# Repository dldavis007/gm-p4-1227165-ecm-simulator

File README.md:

# BUA / GM 1227165 Step-171 evidence-supported whole-image closure

## Current status

The supplied 9340 / 16059335 PROM image has an evidence-supported behavioral
C89 translation with no known reachable, internally defined executable area
remaining classified as unported. This is not a claim of cycle-exact processor
emulation or electrical equivalence to the original ECM.

- [Current project status](docs/CURRENT_PROJECT_STATUS.md)
- [Formal theory of operation](THEORY_OF_OPERATION.md)
  ([PDF publication](THEORY_OF_OPERATION.pdf))
- [Documentation hub](docs/README.md)
- [Simulator, build, and testing guide](docs/SIMULATOR_BUILD_TEST_GUIDE.md)
- [Embedded and HIL implementation roadmap](docs/EMBEDDED_HIL_IMPLEMENTATION_ROADMAP.md)
- [Step history index](docs/STEP_HISTORY_INDEX.md)
- [Technical-reference index](docs/reference/README.md)
- [Step 171 closure audit](docs/STEP171_WHOLE_IMAGE_RECLOSURE_AUDIT.txt)

New behavioral work requires a newly identified exact listing discrepancy or
new primary evidence. Embedded/HIL implementation is a separate phase at the
documented HAL boundaries.

## Development history

This retains the modular frozen Step-104 C89 PC harness, independent Step-105
transmission-aware driving scenario, and Step-106 listing correction.  Step
107 begins the listing-backed translation of Major Segment D diagnostics,
Step 108 translates its complete `LE4F7..LE75C` qualification chain, and Step
109 completes the field-service and flash-code routes and scheduler wiring.
Step 110 audits the remaining executable image and completes the listing-exact
Segment-1 MPU/I/O output staging at `$EDA3..$EF03`. Step 111 translates and
scheduler-wires the key-off front at `$D6D1..$D769`, the LF447 block-learn
commit, the IAC reset/park state machine at `$D370..$D3DB`, and a thin HAL
event at the software-powerdown endpoint.
Step 112 adds a listing-only, source-ordered model of `$C800..$C9F3`, including
the normal scheduler handoff and explicit boundaries for factory test, the
optional HUD ROM, SWI wait, MPU peripherals, and 8192-baud service. It does
not use `bua-hac.txt` as firmware evidence.
Step 113 translates the exact LF3A7 retained-error checksum and LF434 BLM/SAM
initialization, corrects the live LF434 default from historical decimal 120 to
the emitted `$80` (128), and preserves the older value only inside explicit
Step-104/105/109 signature replays.
Step 114 integrates the listing-ordered normal startup initializer at
`$C93B..$C9F3` through a distinct power-on entry point. It reuses established
coolant, TPS and Segment-E behavior, preserves the direct SCI/MPU/timer writes,
and leaves the unresolved SCI device-control-block walk as a named boundary.
Step 115 resolves that device-control-block initialization and translates the
listing's sole device `$80` receive, validation, checksum, Modes 0–4, response,
and transmit-state core. Physical byte timing and unrepresented ROM reads stay
behind explicit PC/HAL boundaries.
Step 116 connects completed SCI messages to the source-ordered `$CB5F..$CBB4`
Mode-4 scheduler lifecycle and `$CBCA..$CBD9` communication timeout. Mode-4
activation now occurs after reception, and entry-only error, IAC and BLM reset
commands execute exactly once.
Step 117 integrates the factory-test boot and IRQ control path at
`$C8B2..$C8DF`, `$CA6F..$CA73`, and `$FC72..$FD28`. It preserves the emitted
factory data-pointer table, optional `$AA` RAM fill, FMD exchange boundary,
96-count minor loop, serial cadence selection, battery/ignition decisions, and
literal COP restart. Custom-control and physical output exercises beginning at
`$FD29` remain a separate hardware-facing step.
Step 118 completes the listing-backed factory-test execution loop at
`$FD29..$FEA3`. It preserves the raw numeric mode-bit branches, nonvolatile
RAM checksum, twelve-channel A/D capture, alternating coolant pull-up samples,
six-channel PWM exercise, lamp/fan and IAC bit sequences, and the three exact
reference-period fuel/spark branches. Electrical effects and the final wait
loop remain HAL boundaries.
Step 119 preserves the eight emitted vector words at `$FFF0..$FFFE`, connects
the `$C9F4` slot to ordinary/factory IRQ dispatch, confirms `$F27B` is an
immediate `RTI`, and represents the four `$C800` destinations as reset/startup
requests. Both `$6000` targets and the processor-specific SWI-to-slot mapping
remain explicit boundaries rather than comment-derived assumptions.
Step 120 composes the previously audited startup pieces into one live,
source-ordered `$C800..$C9F3` power-on dispatcher. It preserves retained RAM
until validation, clears the exact volatile ranges, selects factory test
before retained recovery, records the absent HUD ROM and `$C938` SWI as
boundaries, and hands normal boots to the Step-114 initializer. ROM checksum,
socket-check result, and hardware samples remain explicit host/HAL inputs.
Step 121 connects reset-vector power-on, normal IRQ operation, ignition-off
shutdown, BLM commit, IAC homing, the software-powerdown boundary, and a later
retained restart in one end-to-end PC/HAL lifecycle. It also proves corrupted
retained recovery and factory-path isolation. Physical power switching and
processor reset consequences remain explicitly acknowledged HAL boundaries.
Step 122 re-audited the complete assembled image after the Step-111 through
Step-121 integrations and initially found no known reachable, internally
defined firmware area still classified as unported. Step 167 later narrowed
that conclusion after identifying the missing LF880 factory and diagnostic
table branches. Steps 168 and 169 translate those exact listing-backed gaps,
Step 170 exposes the completed manager through a cell-level raw HAL, and Step
171 restores the qualified whole-image closure conclusion. Remaining limits
are calibration/data, external or absent ROM, processor/custom-device behavior,
and physical electrical/timing boundaries rather than known unported behavior.
Step 123 inventories the historical Library/Drive evidence before cleanup. It
confirms the committed assembled listing, identifies the six ECM schematic
sheets and MEMCAL records awaiting controlled import, classifies duplicate
candidates and historical Step packages, and records the missing original
PROM/S-record comparison artifact. It changes no behavioral code and authorizes
no Library deletion.
Step 124 imports one hash-verified copy of each of the six ECM schematic sheets,
the MEMCAL photograph, connection notes, and resistor notes. It proves the
numbered schematic and photograph copies byte-identical, preserves all variant
and provenance limitations, and still authorizes no historical-file deletion.
Step 125 audits seven unique historical Step-104/105/109/110/111 packages,
proves the two Step-111 ZIPs byte-identical, and records how their source,
output, warning, audit, and signature content relates to the active repository.
The redundant packages are intentionally not committed. It changes no
behavioral code and performs no historical-file deletion.
Step 126 closes the MEMCAL/source-provenance investigation supportable from the
retained evidence. It clarifies the 66-contact MEMCAL carrier, documents the
14-terminal 16055375 and 16-terminal 16055376 network reconstructions and their
zero-ohm routing-jumper scheme, adds historical package-geometry corroboration,
and verifies the corrected `bua-hac.asm -> bua-hac.lst / bua-hac.s19 /
bua-hac.bin` build relationship. The authoritative listing remains the primary
repository byte/address evidence. Physical carrier continuity and installed-
resistor checks remain explicitly deferred hardware measurements rather than
Step-126 blockers.
Step 127 classifies the remaining hardware-facing simulator interfaces by
fidelity: listing-exact firmware/raw-register behavior, schematic-connected
hardware, processor-visible HAL signals, simulator-only plant/transfer
assumptions, and external/unknown device boundaries. It confirms that no new
translated-core behavior is required by the current evidence and prioritizes
explicit HAL setters/observers as the safest next implementation work.
Step 128 adds that explicit HAL seam around already-established raw inputs and
outputs. It introduces named setters/observers for O2, battery, VSS, reference
RPM, bounded RAM, MPU, parallel-I/O and related raw state without adding new
electrical semantics, vehicle-plant behavior, or custom-device assumptions.
Step 129 converts the reverse-engineered MEMCAL resistor networks from generic
grid layouts into functional terminal-level networks, closes the physical
66-pin carrier-to-J4 mapping, and establishes photograph-first authority for
as-built resistor and zero-ohm-jumper population. It also closes the 16055376
24-kOhm discrepancy in favor of the photographed hardware and LTspice model.
Step 130 carries those MEMCAL mappings through the motherboard and into
listing-backed firmware behavior. It establishes evidence-linked CAL42/OSC,
CAL56/CYL, CAL61/MAP, CAL59/VIGN and ESC/KNOCK paths while keeping U11/U12
internal transfer functions and resistor-only semantics explicitly unresolved.
Step 131 traces the visible ignition and injection chain around U9, U11 and
U12. It attributes the `$3FC0-$3FFF` window to U9 at the device level, closes
the supported processor-visible reference/RPM, spark/EST and injector-command
paths, and leaves exact pin-to-register mapping, polarity, phase and current
control as custom-device boundaries.
Step 132 separates the physical MAP/MAP2 and CAL61/U11 paths from the supplied
image's actual MAF/reference-period load producer. It establishes `$0063` as a
MAF-derived load quantity for this image and preserves U11 MAP/CAL61 behavior
and variant-dependent MAP use as unresolved.
Step 133 maps the visible U10 A/D channels to schematic signals, normal
firmware selectors, factory-test capture, raw RAM state and processed behavior.
It distinguishes MAP2, VOLT, O2, MAP, CTS, TPS, PUMPVOLT, DIAG, MAT, ESC and
VMAF channels and records which selectors the normal image actually requests.
Step 134 separates CAL42/U11 OSC, CAL56/U12 CYL and the distributor-reference
path. It cross-references reference occurrence, period and RPM processing while
preserving U11/U12/U9 internal behavior and CAL56 voltage encoding as explicit
unknowns.
Step 135 separates the CAL29/U10 analog ESC monitor from the CAL32/U12/U9
knock-event path and traces the executable knock-retard, recovery, spark
subtraction and Error-43 behavior. The U9 KNOCK-pin-to-`$3FCA` relationship is
kept as a strong inference rather than promoted to undocumented direct proof.

The project targets the 1986 Corvette L98 GM P4 ECM, service number 1227165, using the
supplied 9340 / 16059335 PROM material.  `BUA` remains a source label, not an
independently proven calibration identity.

## Build

The project deliberately builds as one translation unit:

```text
gcc -std=c89 -Wall -Wextra -pedantic main.c -o build/bua_step121
```

The included implementation fragments must not be compiled separately.
`main.c` includes them in the frozen declaration order so all existing
file-local (`static`) linkage and arithmetic behavior remain unchanged.

- Windows compile: run `build_gcc.bat`
- Windows compile and run: run `build_run_gcc.bat`
- Linux/macOS compile and run: run `sh build_gcc.sh`
- Make: run `make test`

For OnlineGDB, import the complete project tree and compile only `main.c`.
Every source fragment is well below the previously observed approximately
11,000-line editor/save limit.  `main.c` itself contains `int main(void)`.

## Directory layout

| Path | Purpose |
| --- | --- |
| `main.c` | Readable include map and program entry point |
| `src/` | Translated ECM algorithms, scheduler, RAM/MPU model, and feature wiring |
| `simulation/` | Original scripted drive plus the PC-only transmission-aware plant |
| `tests/` | Regression models and regression functions |
| `docs/` | Frozen evidence and numbered step audits |
| `docs/reference/` | Living evidence register, hardware/firmware cross-reference, MEMCAL model, and theory-of-operation index |
| `evidence/firmware/` | Authoritative assembled listing and corrected-source/build provenance record |
| `evidence/hardware/` | Hash-identified ECM schematic evidence with provenance and interpretation limits |
| `evidence/memcal/` | Hash-identified MEMCAL photograph, connection notes, resistor evidence, and reconstruction records |
| `build/` | Generated executables, output, and compiler diagnostics |

Files ending in `.inc.h` are implementation fragments, not independent public
headers.  The naming makes that constraint explicit while preventing online
compilers from treating them as separate C source files.

## Behavioral baselines

- Frozen Step-104 behavioral signature: `4BA6B7C6`
- Step-105 transmission trace signature: `9732D09B`
- Step-106 listing-coolant regression: 12/12
- Step-107 diagnostic-stage regression: 17/17
- Step-108 diagnostic-qualification regression: 22/22
- Step-109 integrated Segment-D regression: 40/40
- Step-109 integrated Segment-D signature: `F357A5F2`
- Step-110 Segment-1 output regression: 22/22
- Step-110 integrated output-stage signature: `FAADF8A6`
- Step-111 ignition shutdown/IAC homing regression: 40/40
- Step-111 ignition lifecycle signature: `16D17C9C`
- Step-112 source-ordered reset/startup regression: 19/19
- Step-113 retained-memory/startup regression: 10/10
- Step-114 source-ordered normal-startup regression: 14/14
- Step-115 8192-baud SCI/message regression: 20/20
- Step-116 Mode-4 lifecycle/scheduler regression: 16/16
- Step-117 factory-test boot/control regression: 24/24
- Step-118 factory-test execution regression: 31/31
- Step-119 vector/exception-boundary regression: 19/19
- Step-120 unified power-on-dispatch regression: 24/24
- Step-121 end-to-end ignition-lifecycle integration: 18/18
- Step-158 normal-operation FMD raw HAL regression: 7/7
- Step-159 raw-HAL lifecycle integration regression: 8/8
- Step-160 full raw-HAL lifecycle integration regression: 13/13
- Step-160 full raw-HAL lifecycle signature: `2E92563C`
- Step-161 raw-HAL output lifecycle regression: 9/9
- Step-161 raw-HAL output lifecycle signature: `B22B98ED`
- Step-162 raw-VOLT output-safety regression: 10/10
- Step-162 raw-VOLT output-safety signature: `DB86F332`
- Step-163 raw-HAL power-on composition regression: 10/10
- Step-163 raw-HAL power-on signature: `040E3A8B`
- Step-164 raw-HAL factory IRQ regression: 10/10
- Step-164 raw-HAL factory IRQ signature: `0194B153`
- Step-165 raw-HAL factory A/D regression: 9/9
- Step-165 raw-HAL factory A/D signature: `0EACFF4F`
- Step-166 8192-baud SCI raw-HAL regression: 9/9
- Step-166 8192-baud SCI raw-HAL signature: `52396771`
- Step-168 diagnostic 160-baud manager regression: 6/6
- Step-169 factory 160-baud manager regression: 8/8
- Step-170 complete 160-baud raw-HAL regression: 9/9
- Strict C89 compile: no warnings
- Integrated drive regression: 26/26
- Step-104 freeze regression: 10/10
- Step-105 transmission-aware regression: 12/12

The original Step-104 scenario remains present and unchanged.  Step 105 runs
after a fresh reset and derives Drive RPM from vehicle speed, selected ratio,
converter slip, and physical TCC state.  Its shift points, slip, and combined
axle/tire factor are explicitly simulator parameters, not factory claims.

The listing proves that LF42A is an RTS at $F42A.  It also proves that the
assembled ERR14/15 fallback at $F418 branches to LF42A; the `COOLS8` spelling
in the supplied text is not an unresolved executable destination.

See `docs/STEP121_LIFECYCLE_INTEGRATION_AUDIT.txt` for the end-to-end lifecycle
integration audit and `docs/STEP122_WHOLE_IMAGE_CLOSURE_AUDIT.txt` for the
post-integration coverage conclusion. See
`docs/STEP123_LIBRARY_EVIDENCE_INVENTORY.txt` for the pre-cleanup archive gate.
See `docs/STEP124_CONTROLLED_EVIDENCE_IMPORT.txt` for the imported artifact
manifest and duplicate proof. See
`docs/STEP125_HISTORICAL_PACKAGE_AUDIT.txt` for the package-level
manifest and preservation decisions. See
`docs/STEP126_MEMCAL_AND_SOURCE_PROVENANCE_CLOSURE_AUDIT.txt` for the MEMCAL,
corrected-source, build-output, and historical-PROM provenance closure. See
`docs/STEP127_HARDWARE_HAL_FIDELITY_AUDIT.txt` for the hardware/HAL fidelity
classification. See `docs/STEP128_EXPLICIT_HAL_INTERFACE_AUDIT.txt` for the
explicit raw HAL boundary and `docs/STEP129_MEMCAL_FUNCTIONAL_NETWORK_AUDIT.txt`
for the functional MEMCAL reconstruction and physical carrier mapping. See
`docs/STEP130_MEMCAL_MOTHERBOARD_FIRMWARE_CROSS_REFERENCE_AUDIT.txt` through
`docs/STEP135_ESC_KNOCK_SIGNAL_CHAIN_AUDIT.txt` for the current motherboard,
custom-device, sensor-acquisition, timing and ESC/knock theory-of-operation
cross-reference work. See `docs/STEP158_NORMAL_FMD_RAW_HAL_AUDIT.txt` for the
normal-operation FMD/SPI raw-input boundary and
`docs/STEP159_RAW_HAL_LIFECYCLE_INTEGRATION_AUDIT.txt` for its integration with
the raw VOLT ignition path. See
`docs/STEP160_FULL_RAW_HAL_LIFECYCLE_AUDIT.txt` for the full key-off, IAC homing,
powerdown, and retained-restart acceptance cycle, and
`docs/STEP161_RAW_HAL_OUTPUT_LIFECYCLE_AUDIT.txt` for the corresponding raw
output-window shutdown and restart contract, and
`docs/STEP162_RAW_VOLT_OUTPUT_SAFETY_AUDIT.txt` for the scheduler-driven
two-pass overvoltage output shutdown, and
`docs/STEP163_RAW_HAL_POWER_ON_COMPOSITION_AUDIT.txt` for raw VOLT, PUMPVOLT,
DIAG, and FMD startup selection, and
`docs/STEP164_RAW_HAL_FACTORY_IRQ_AUDIT.txt` for continued raw-input ownership
during factory IRQ execution, and
`docs/STEP165_RAW_HAL_FACTORY_ADC_AUDIT.txt` for the live eleven-channel named
factory sweep with the unidentified `$B0` slot preserved, and
`docs/STEP166_SCI8192_RAW_HAL_AUDIT.txt` for the message-level receive/response
boundary around the translated 8192-baud SCI core, and
`docs/STEP167_ALDL160_COMPLETENESS_AUDIT.txt` for the corrected scope of the
normal, diagnostic and factory 160-baud byte-manager paths.
Steps 168 and 169 close both table-manager gaps;
`docs/STEP170_ALDL160_RAW_HAL_AUDIT.txt` records the resulting cell-level raw
HAL boundary, and `docs/STEP171_WHOLE_IMAGE_RECLOSURE_AUDIT.txt` reconciles the
whole-image closure conclusion. Earlier audits remain historical checkpoints.

Normal simulator execution now runs Segment D once per 16 ordinary IRQs. The
PC-only `sim_legacy_segment_d_freeze` switch is enabled only inside the frozen
Step-104 and Step-105 replay scenarios, so their historical signatures remain
comparable. It is not source RAM and is not part of the target ECM behavior.

Normal simulator execution now also performs Segment 1's raw writes to MPU
addresses `$3FCC/$3FD2/$3FD4/$3FD6/$3FD8` and parallel-I/O `$4004`. Electrical
polarity and the physical output devices remain HAL responsibilities. The
PC-only Segment-1 replay switch is used only by frozen historical signatures.

Ordinary odd minor loops now run the literal ignition-on/key-off front before
the existing load/fuel chain. Ordinary even minor loops run the IAC homing
producer after reference/RPM/spark work, while the existing motor consumer
continues every 6.25 ms. At `$D6EA`, the PC HAL records one software-powerdown
event and stops subsequent IRQ dispatch; physical keep-alive power remains a
hardware integration responsibility.

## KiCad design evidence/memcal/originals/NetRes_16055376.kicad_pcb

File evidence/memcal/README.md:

# MEMCAL evidence

This directory contains source evidence and reconstruction records for the BUA /
GM 1227165 MEMCAL (memory/calibration) work.

## As-built prototype photographs

The reconstructed MEMCAL prototype photographs are committed under
`evidence/memcal/photos/` and are the authoritative as-built evidence whenever
component markings, jumper population, opens, orientation, or physical routing
are legible in the photographs.

- [`photos/reverse_engineered_memcal_overview.jpg`](photos/reverse_engineered_memcal_overview.jpg)
  — full-resolution, broadly viewable overall reconstructed MEMCAL prototype
  view.
- [`photos/reverse_engineered_memcal_resistor_board_closeup.jpg`](photos/reverse_engineered_memcal_resistor_board_closeup.jpg)
  — full-resolution, broadly viewable close-up used for the 16055375 / 16055376
  resistor-network and jumper audit.

The original `.heic` files remain beside the JPEGs as archival source files. The
JPEGs preserve the original 4032 x 3024 pixel dimensions, have metadata removed,
and are the preferred copies for GitHub and ordinary source-code editors.

Where the photographed as-built hardware conflicts with KiCad, LTspice,
historical notes, or derived models, the photograph controls the as-built
reconstruction and the discrepancy should be retained rather than silently
normalized.

## Supporting records

- `MEMCAL_16055375_RECONSTRUCTION_RECORD.md`
- `MEMCAL_16055375_TOPOLOGY_AUDIT.md`
- `MEMCAL_16055376_RECONSTRUCTION_RECORD.md`
- `MEMCAL_16055376_AS_BUILT_PHOTO_AUDIT.md`
- `MEMCAL_16055376_TOPOLOGY_AUDIT.md`
- `MemCal photo 86 Vette BUA.png` — original/reference MEMCAL photograph.
- `MemCal, Cal connections.docx`
- `Resistors.txt`

See `docs/reference/MEMCAL_EVIDENCE_HIERARCHY.md` for the project-wide evidence-priority rule and the numbered STEP audit documents for the chronological reconstruction history.

## Original models and resistance workbook

The `originals/` directory preserves both LTspice drawings, both KiCad
PCB/schematic/project sets and the original ODS resistance workbook.
See the [manifest](../../docs/ORIGINAL_EVIDENCE_MANIFEST.md) and
[Step-178 audit](../../docs/STEP178_ORIGINAL_EVIDENCE_PRESERVATION_AUDIT.md).
The recovered workbook raises unresolved cross-terminal discrepancies for the
16055375 candidate; full electrical equivalence is not established.

## Original measurement targets and new candidates

The owner confirmed the workbook as original-device measurements and the
replacement target. The earlier hand reconstruction is approximate.
See [fitted candidates](fitted_models/README.md) and
[engineering report](../../docs/NETRES_MEASURED_MATRIX_RECONSTRUCTION.md).

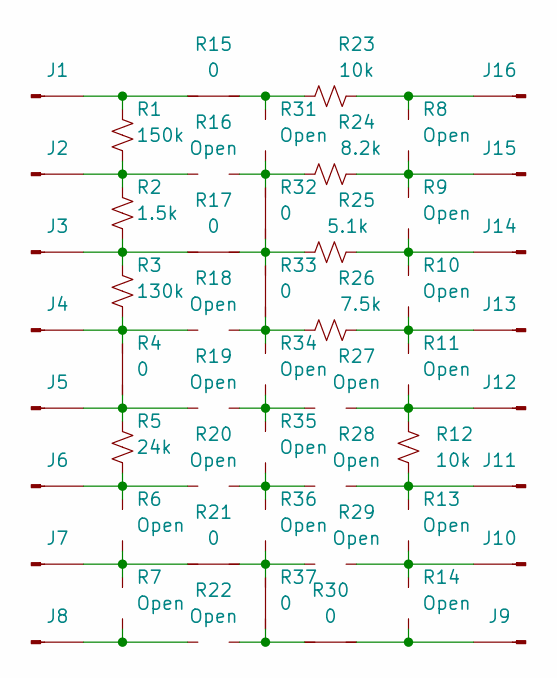
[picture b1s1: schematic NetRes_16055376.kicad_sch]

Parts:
J1, J2, J3, J4, J5, J6, J7, J8, J9, J10, J11, J12, J13, J14, J15, J16: Conn_01x01_Pin; Pin_D0.7mm_L6.5mm_W1.8mm_FlatFork
R1: 150k; R_0603_1608Metric
R2: 1.5k; R_0603_1608Metric
R3: 130k; R_0603_1608Metric
R4, R15, R17, R21, R30, R32, R33, R37: 0; R_0603_1608Metric
R5: 24k; R_0603_1608Metric
R6, R7, R8, R9, R10, R11, R13, R14, R16, R18, R19, R20, R22, R27, R28, R29, R31, R34, R35, R36: Open; R_0603_1608Metric
R12, R23: 10k; R_0603_1608Metric
R24: 8.2k; R_0603_1608Metric
R25: 5.1k; R_0603_1608Metric
R26: 7.5k; R_0603_1608Metric

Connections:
unnamed: J1.1, R1.1, R15.1
unnamed: J2.1, R1.2, R2.1, R16.1
unnamed: J3.1, R2.2, R3.1, R17.1
unnamed: J4.1, R3.2, R4.1, R18.1
unnamed: J5.1, R4.2, R5.1, R19.1
unnamed: J6.1, R5.2, R6.1, R20.1
unnamed: J7.1, R6.2, R7.1, R21.1
unnamed: J8.1, R7.2, R22.1
unnamed: J9.1, R14.2, R30.2
unnamed: J10.1, R13.2, R14.1, R29.2
unnamed: J11.1, R12.2, R13.1, R28.2
unnamed: J12.1, R11.2, R12.1, R27.2
unnamed: J13.1, R10.2, R11.1, R26.2
unnamed: J14.1, R9.2, R10.1, R25.2
unnamed: J15.1, R8.2, R9.1, R24.2
unnamed: J16.1, R8.1, R23.2
unnamed: R15.2, R23.1, R31.1
unnamed: R16.2, R24.1, R31.2, R32.1
unnamed: R17.2, R25.1, R32.2, R33.1
unnamed: R18.2, R26.1, R33.2, R34.1
unnamed: R19.2, R27.1, R34.2, R35.1
unnamed: R20.2, R28.1, R35.2, R36.1
unnamed: R21.2, R29.1, R36.2, R37.1
unnamed: R22.2, R30.1, R37.2

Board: 2 copper layers, 53 parts (0 on the bottom side), 24 nets, no tracks yet.
